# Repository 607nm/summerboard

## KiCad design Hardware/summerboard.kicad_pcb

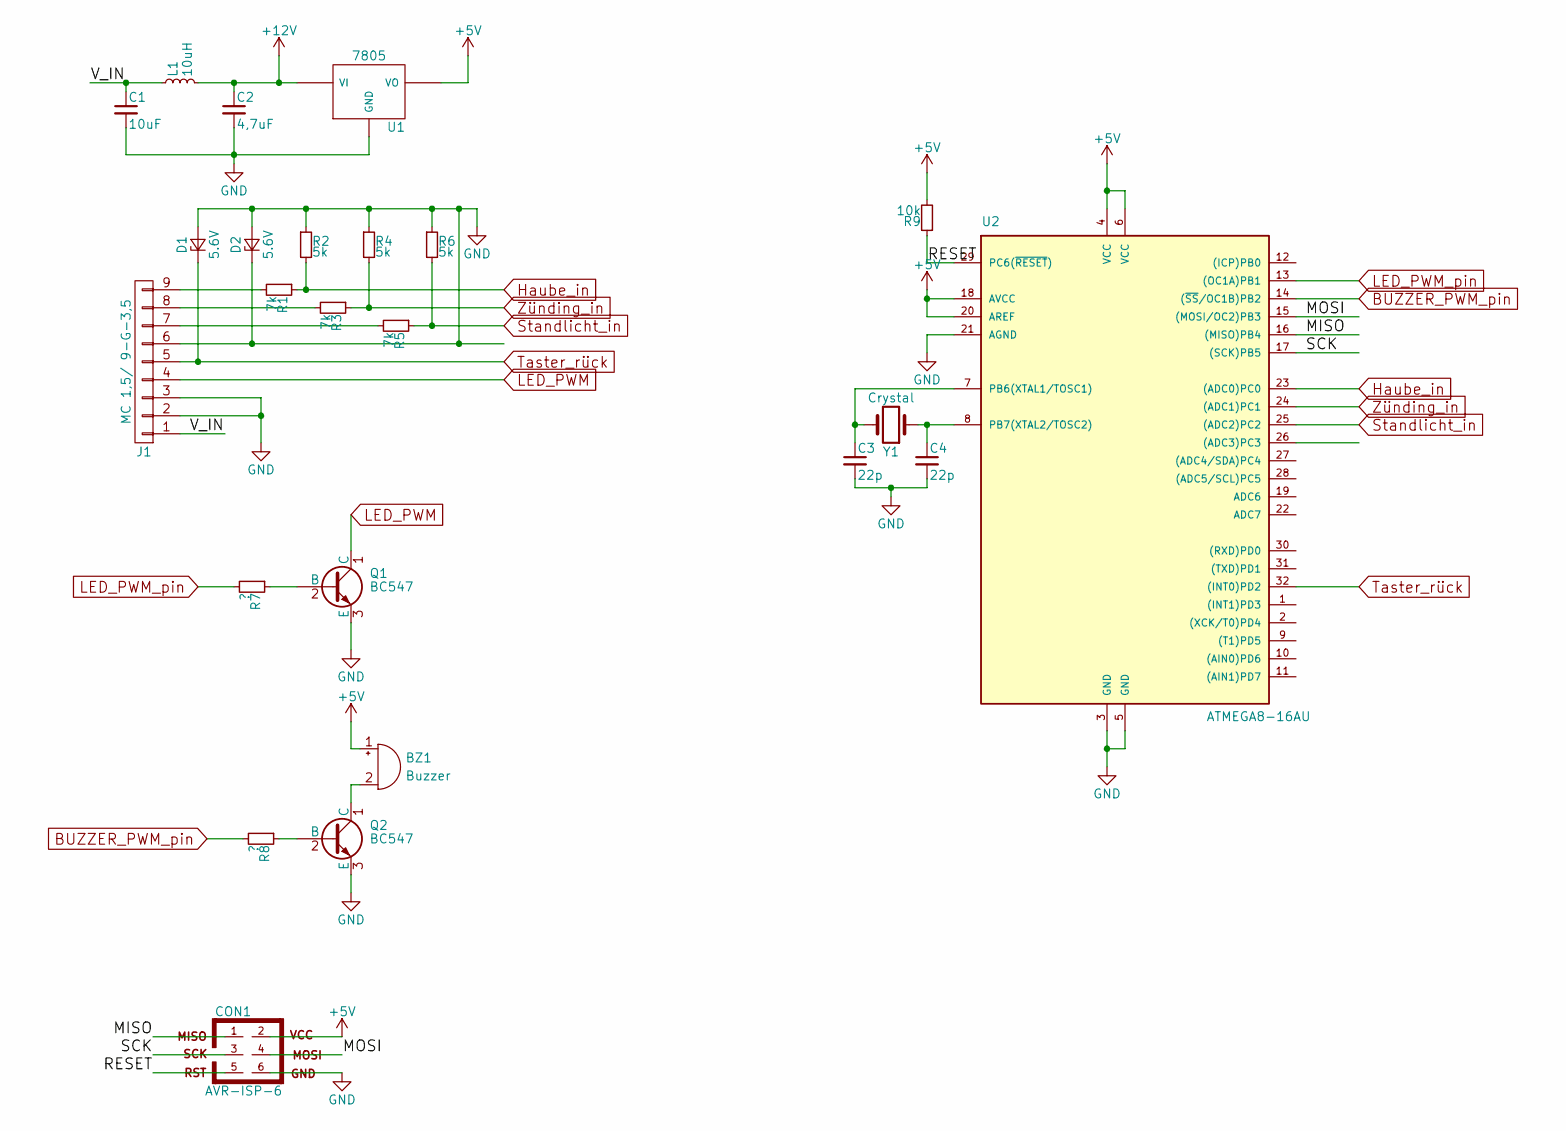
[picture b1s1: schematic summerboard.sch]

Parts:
BZ1: Buzzer; Buzzer_12x9.5RM7.6
C1: 10uF; R_0805_HandSoldering
C2: 4,7uF; R_0805_HandSoldering
C3, C4: 22p; R_0805_HandSoldering
CON1: AVR-ISP-6; JAE_LY20-06P-2T_2x03x2.00mm_Straight
D1, D2: 5.6V; D_SOT-23_ANK
J1: MC 1,5/ 9-G-3,5; MCV1,5_09-GF-3,5-LR
L1: 10uH; R_1210_HandSoldering
Q1, Q2: BC547; TO-92_Molded_Narrow
R1, R3, R5: 7k; R_0603_HandSoldering
R2, R4, R6: 5k; R_0603_HandSoldering
R7, R8: ?; R_0603_HandSoldering
R9: 10k; R_0603_HandSoldering
U1: 7805; RECOM-R-78xx-0.5
U2: ATMEGA8-16AU; TQFP-32_7x7mm_Pitch0.8mm
Y1: Crystal; Crystal_HC18-U_Vertical

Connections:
+5V: BZ1.1 (-), CON1.2, R9.2, U1.VO, U2.4 (VCC), U2.6 (VCC), U2.18 (AVCC), U2.20 (AREF)
+12V: C2.1, L1.2, U1.VI
/MISO: CON1.1, U2.16 ((MISO)PB4)
/MOSI: CON1.4, U2.15 ((MOSI/OC2)PB3)
/RESET: CON1.5, R9.1, U2.29 (PC6(~RESET~))
/SCK: CON1.3, U2.17 ((SCK)PB5)
/V_IN: C1.1, J1.1, L1.1
BUZZER_PWM_pin: R8.2, U2.14 ((~SS~/OC1B)PB2)
GND: C1.2, C2.2, C3.2, C4.2, CON1.6, D1.2 (A), D2.1 (K), D2.2 (A), J1.2, J1.3, J1.6, Q1.3 (E), Q2.3 (E), R2.1, R4.1, R6.1, U1.GND, U2.3 (GND), U2.5 (GND), U2.21 (AGND)
Haube_in: R1.1, R2.2, U2.23 ((ADC0)PC0)
LED_PWM: J1.4, Q1.1 (C)
LED_PWM_pin: R7.2, U2.13 ((OC1A)PB1)
unnamed: BZ1.2 (+), Q2.1 (C)
unnamed: C3.1, U2.7 (PB6(XTAL1/TOSC1)), Y1.2
unnamed: C4.1, U2.8 (PB7(XTAL2/TOSC2)), Y1.1
unnamed: J1.7, R5.2
unnamed: J1.8, R3.2
unnamed: J1.9, R1.2
unnamed: Q1.2 (B), R7.1
unnamed: Q2.2 (B), R8.1
Standlicht_in: R5.1, R6.2, U2.25 ((ADC2)PC2)
Taster_rück: D1.1 (K), J1.5, U2.32 ((INT0)PD2)
Zünding_in: R3.1, R4.2, U2.24 ((ADC1)PC1)

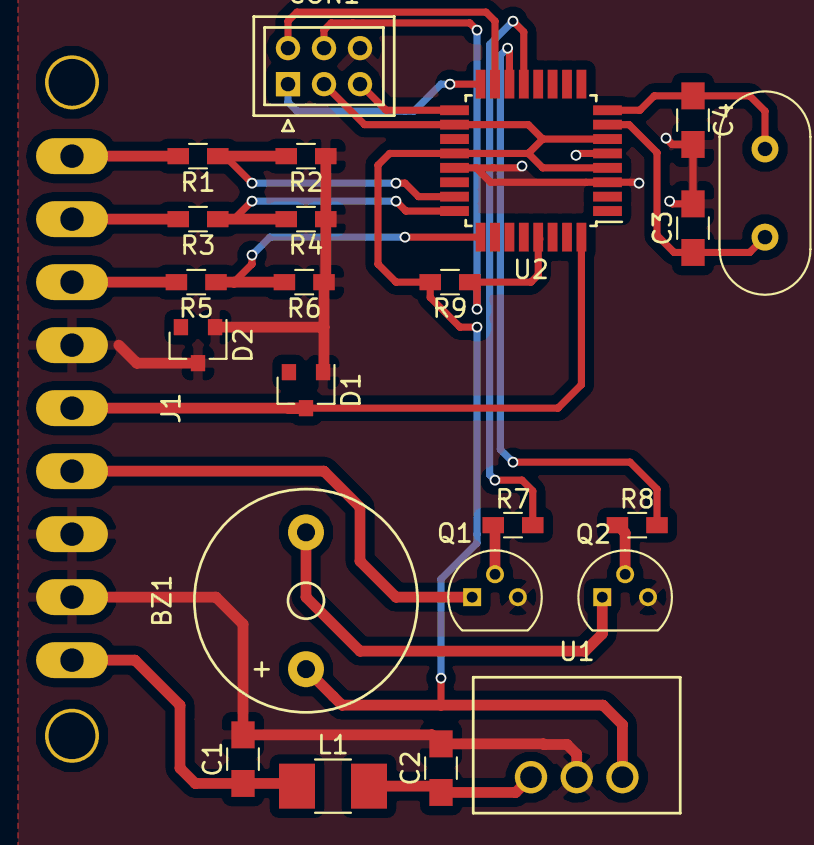
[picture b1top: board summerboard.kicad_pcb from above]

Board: 2 copper layers, 24 parts (0 on the bottom side), 23 nets.

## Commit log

2017-06-26 create pcb
